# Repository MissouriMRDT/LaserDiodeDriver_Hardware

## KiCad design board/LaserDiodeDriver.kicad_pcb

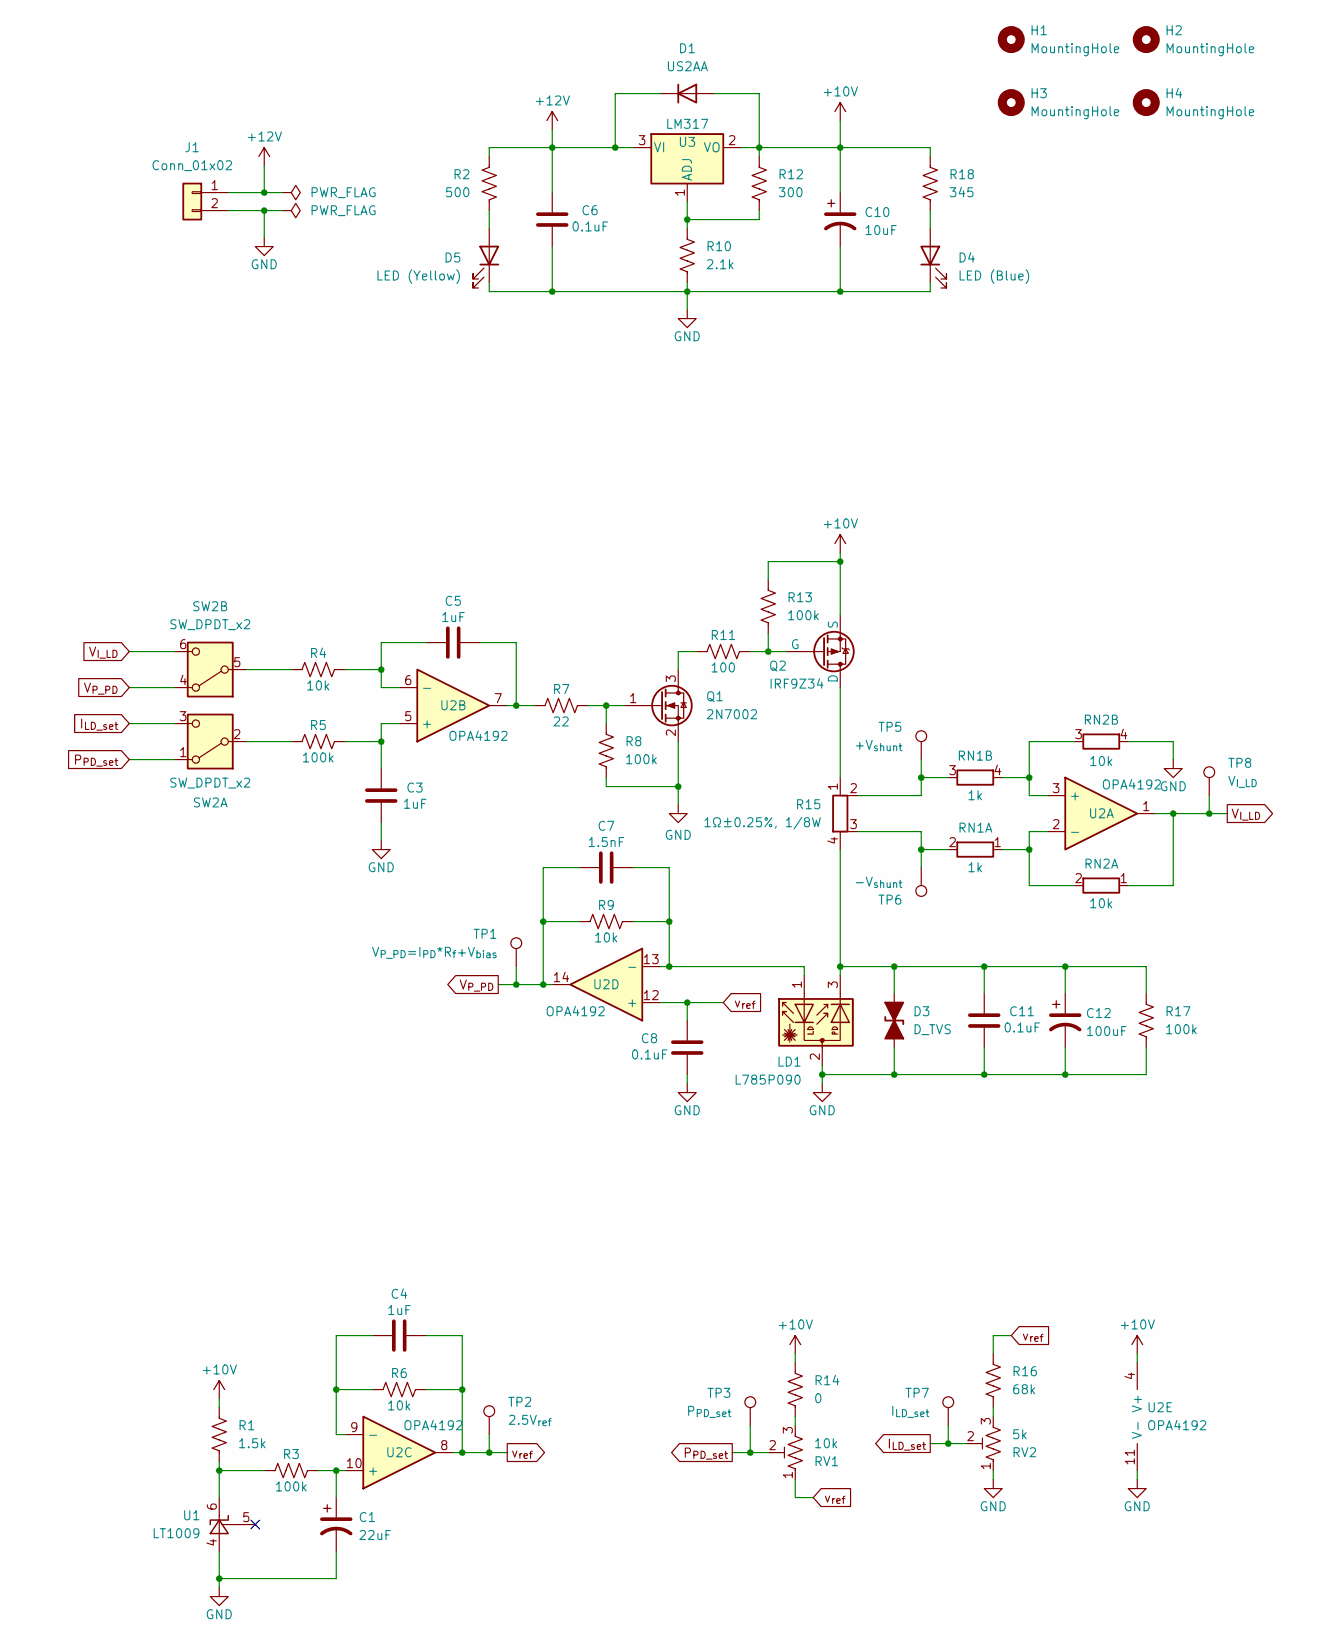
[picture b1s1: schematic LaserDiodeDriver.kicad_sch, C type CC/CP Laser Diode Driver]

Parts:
C1: 22uF; CP_Elec_5x5.8
C3, C4, C5: 1uF; C_0603_1608Metric
C6, C8, C11: 0.1uF; C_0603_1608Metric
C7: 1.5nF; C_0603_1608Metric
C10: 10uF; CP_Elec_5x5.8
C12: 100uF; CP_Elec_6.3x5.8
D1: US2AA; D_SMA
D3: D_TVS; D_0603_1608Metric
D4: LED (Blue); LED_0603_1608Metric
D5: LED (Yellow); LED_0603_1608Metric
H1, H2, H3, H4: MountingHole; Mounting_Wuerth_WA-SMSI-M1.6_H4.5mm_ThreadDepth2mm_97730456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
J1: Conn_01x02; JST_EH_S2B-EH_1x02_P2.50mm_Horizontal
LD1: L785P090; S7060R - Laser Diode Socket for Ø5.6 mm Laser, 3 Pin
Q1: 2N7002; SOT-23
Q2: IRF9Z34; TO-220-3_Horizontal_TabUp
R1: 1.5k; R_0603_1608Metric
R2: 500; R_0603_1608Metric
R3, R5, R8, R13, R17: 100k; R_0603_1608Metric
R4, R6, R9: 10k; R_0603_1608Metric
R7: 22; R_0603_1608Metric
R10: 2.1k; R_0603_1608Metric
R11: 100; R_0603_1608Metric
R12: 300; R_0603_1608Metric
R14: 0; R_0603_1608Metric_Pad0.98x0.95mm_HandSolder
R15: 1Ω±0.25%, 1/8W; R_Shunt_0805_2012Metric
R16: 68k; R_0603_1608Metric_Pad0.98x0.95mm_HandSolder
R18: 345; R_0603_1608Metric
RN1: 1k; R_Array_Convex_2x0606
RN2: 10k; R_Array_Convex_2x0606
RV1: 10k; Potentiometer_Bourns_3296W_Vertical
RV2: 5k; Potentiometer_Bourns_3296Y_Vertical
SW2: SW_DPDT_x2; SW_DPDT_CK_JS202011JCQN
TP1: V_{P_PD}=I_{PD}*R_{f}+V_{bias}; TestPoint_Pad_D1.5mm
TP2: 2.5V_{ref}; TestPoint_Pad_D1.5mm
TP3: P_{PD_set}; TestPoint_Pad_D1.5mm
TP5: +V_{shunt}; TestPoint_Pad_D1.5mm
TP6: -V_{shunt}; TestPoint_Pad_D1.5mm
TP7: I_{LD_set}; TestPoint_Pad_D1.5mm
TP8: V_{I_LD}; TestPoint_Pad_D1.5mm
U1: LT1009; SOIC-8_3.9x4.9mm_P1.27mm
U2: OPA4192; SOIC-14_3.9x8.7mm_P1.27mm
U3: LM317; TO-220-3_Horizontal_TabUp

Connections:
+10V: C10.1, D1.2 (A), Q2.3 (S), R1.1, R12.1, R13.1, R14.1, R18.1, U2.4 (V+), U3.2 (VO)
+12V: C6.1, D1.1 (K), J1.1, R2.1, U3.3 (VI)
GND: C1.2, C3.1, C6.2, C8.2, C10.2, C11.2, C12.2, D3.1 (A1), D4.1 (K), D5.1 (K), J1.2, LD1.2, Q1.2 (S), R8.2, R10.2, R17.2, RN2.4 (R2.2), RV2.1, U1.4 (A), U2.11 (V-)
I_{LD_set}: RV2.2, SW2.3 (C), TP7.1
unnamed: C5.2, R7.1, U2.7
unnamed: C11.1, C12.1, D3.2 (A2), LD1.3, R15.4, R17.1
unnamed: D4.2 (A), R18.2
unnamed: D5.2 (A), R2.2
unnamed: Q1.3 (D), R11.1
unnamed: Q1.1 (G), R7.2, R8.1
unnamed: Q2.1 (D), R15.1
unnamed: Q2.2 (G), R11.2, R13.2
unnamed: R1.2, R3.1, U1.6 (K), U1.8 (K)
unnamed: R14.2, RV1.3
unnamed: R16.2, RV2.3
unnamed: RN1.1 (R1.1), RN2.2 (R1.2), U2.2 (-)
unnamed: R15.3, RN1.2 (R1.2), TP6.1
unnamed: R15.2, RN1.3 (R2.1), TP5.1
unnamed: RN1.4 (R2.2), RN2.3 (R2.1), U2.3 (+)
unnamed: R5.1, SW2.2 (B)
unnamed: R4.1, SW2.5 (B)
unnamed: C3.2, R5.2, U2.5 (+)
unnamed: C5.1, R4.2, U2.6 (-)
unnamed: C1.1, R3.2, U2.10 (+)
unnamed: C4.1, R6.1, U2.9 (-)
unnamed: C7.2, LD1.1, R9.2, U2.13 (-)
unnamed: R10.1, R12.2, U3.1 (ADJ)
P_{PD_set}: RV1.2, SW2.1 (A), TP3.1
V_{I_LD}: RN2.1 (R1.1), SW2.6 (C), TP8.1, U2.1
V_{P_PD}: C7.1, R9.1, SW2.4 (A), TP1.1, U2.14
v_{ref}: C4.2, C8.1, R6.2, R16.1, RV1.1, TP2.1, U2.8, U2.12 (+)

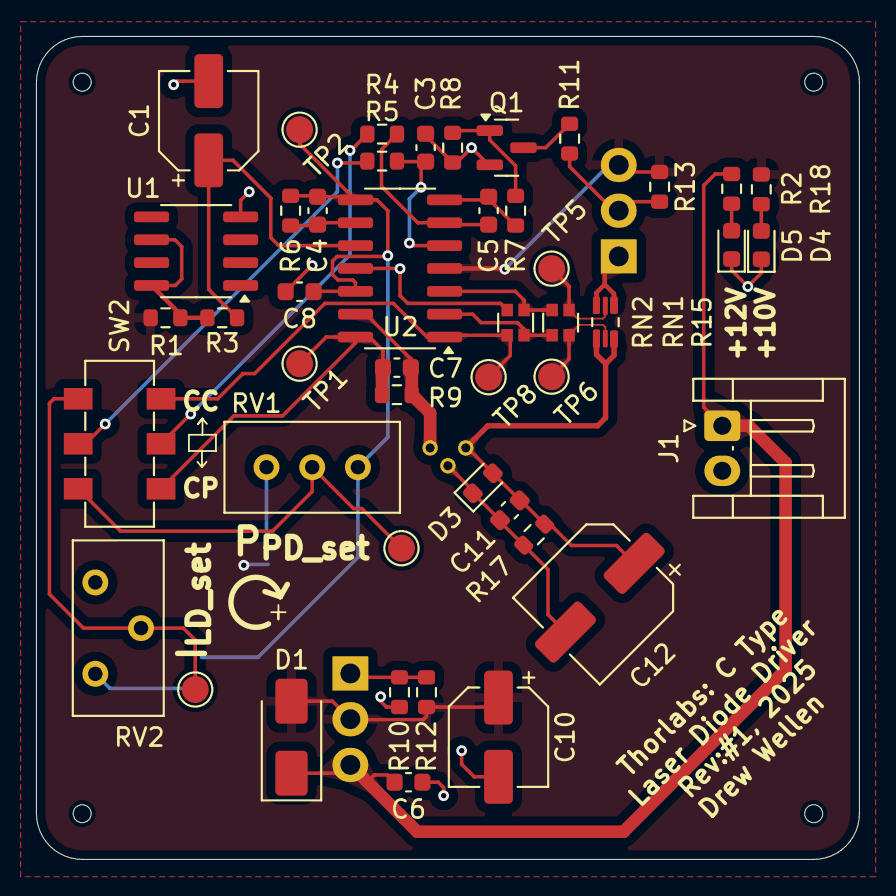
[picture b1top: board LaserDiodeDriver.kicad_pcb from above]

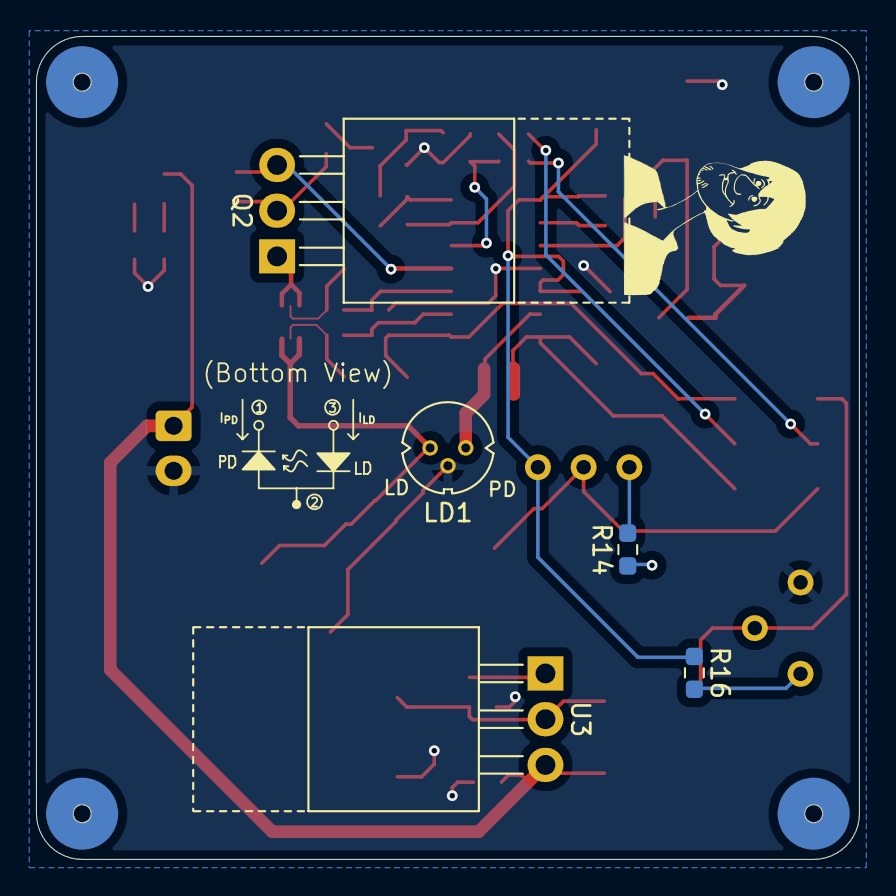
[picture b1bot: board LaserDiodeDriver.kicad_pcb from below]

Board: 2 copper layers, 45.7 x 45.7 mm, 55 parts (9 on the bottom side), 31 nets.

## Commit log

2025-09-07 Added existing schematic
2025-09-15 Updated Parts and Proc'd them
2025-09-16 General changes
2025-09-30 Test circuit
    Started designing the initial test circuit with LM358s to verify the working of a basic P-channel current drive circuit.
2025-10-01 More tweaks to high side current control test circuit
2025-10-02 Designed/Tested a working cathode ground high side current source
2025-10-02 Organizing/editing different circuits
2025-10-03 Move all the test schematics to a local file and started design of the one that will be a board.
2025-10-10 Imported proper working circuit in preparation for layout
2025-10-11 Made/tested LM317 circuit
    The LM317 was configured for 12V input and 6V output to power the main laser driver circuit. With a high power LED as a stand in for the laser diode and current set to 125mA, the power dissipation of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
2025-10-12 Various changes (read description for info)
    * Changed LM317 output voltage to be 10V since testing at that voltage reduced heat dissipation across shunt, LM317, and current drive FET.
    * Deleted test schematic
    * Swapped 1Ohm shunt to five 5Ohm SMD resistors with +_50ppm/*C at 1% tolerance to distribute heat load and average out tolerances.
    * Found proper quad symbol for OP-amp and inserted datasheet + footprint.
2025-10-12 Calculating proper values/picking components
    * Calculated values needed for differential amplifier and Vref max setpoint resistor.
    * Added datasheets, footprints, and descriptions for various parts like pots, shunts, and FET.
    * Tested differential amplifier values on breadboard.
2025-10-14 Constant power loop
    This new circuit uses the same format of constant current loop but now there is a second control loop that can be switched on with a reed relay to incorporate power feedback of the photodiode. This i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
2025-10-14 Idea for differential integrator in one op-amp
2025-10-15 Lots of testing schematics. I am brain dead. Guhhhh
2025-10-15 Tested non-inverting amplifier with offset and confirmed diff amp feedback implausible.
2025-10-16 Tested diff-amp input for gate drive op-amp and added in a summing amplifier to test
2025-10-16 Trying new negative differential feedback for constant power control
2025-10-17 Designed a solid method of photodiode feedback
    This method utilizes a diff-amp with an offset voltage where the photocurrent feedback subtracts from a setpoint and added to the offset to create the current setpoint and regulate the photodiode pow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
2025-10-18 AMAZING DEVELOPMENT!!!
    All of this troubleshooting and different design things come down to a sign issue. It's the fact that the P-channel MOSFET turns off more with a higher voltage at the gate. SO the gate drive op-amp h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
2025-10-18 Got rid of extra schematics and changed page settings
2025-10-18 Tested diff-amp feedback with pull-down transistor for gate driving current control FET. Works!
2025-10-19 Moved diff-amp low to P-channel MOSFET and reduced gain setting resistor values to improve CMRR.
2025-10-20 Eliminated need for mid-rail buffer and cleaned up page. Corrected setpoints.
2025-10-20 Various housekeeping changes
    * Re-did entire schematic to ensure all connections good
    * Added description, datasheet, price, footprint, and part # for almost all parts
    * Cleaned up schematic in general
2025-10-20 Swapped to different signal relay
    Since the signal relay is so large relative to all other components, It may be better to find an alternative. Something quicker than 0 Ohm jumpers but smaller than a telecoms signal relay that still 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
2025-10-20 Added heatsink for P-FET and LM317, slide switch, and power connector
2025-10-20 Found rectifier diode and ensured things fit to begin layout
2025-10-20 Got a footprint, description, price, and datasheet for all parts except laser diode socket
2025-10-21 Made custom footprint/3D model for laser diode socket
2025-10-21 Set height of objects and began rough layout
2025-10-21 Shunt Sense footprint
2025-10-21 Trying goofy layout things
2025-10-21 Final pricing of components $44.88
2025-10-22 Added shunt 3D model
2025-10-22 Changed gate drive feedback capacitor and tested constant power control. Needs improvement.
2025-10-22 Imported power connector models and info.
2025-10-23 Layout of differential amplifier, TIA, and laser diode.
2025-10-23 Added laser diode 3D file and more layout
2025-10-25 Various changes + component placement
    * Removed signal relay in favor of SPDT switch in the interest of space.
    * Placed components for optimal mechanical mounting with LD in center of PCB.
    * Got rid of LM317 pot for space calculated proper values for LM317 to be +10V output.
    * Arranged resistors for good placement.
2025-10-29 Updated switch footprint and added GND filled zone on back.
2025-10-30 Finished Layout
2025-10-30 Added pot indicator silkscreen
2025-10-30 Final touches :)
2025-10-30 Final Final touches. Added indicator LEDs.
2025-10-30 Added date to silkscreen
2025-10-31 Layout review initial changes
2025-11-02 Post layout review fixes. Ready for CDR and ordering
2025-11-11 Add github workflow
2025-11-30 Eliminated unavailable capacitor for a second 10uF electrolytic
2025-12-03 Generated .STEP file
2025-12-07 Flipped laser diode symbol back
2025-12-08 Started simulations in LTspice
2025-12-09 Simulation adjustments and setpoint resistor fixed
2025-12-12 Measured photocurrent and change R14 accordingly
2026-03-15 Began design of rev2
2026-03-15 Added buck components
2026-03-15 Buck converter component selection
2026-03-16 Finished buck converter
2026-03-16 Smaller inductor chosen
2026-03-16 Removed duplicate models
2026-03-16 Moved Rev1 models to Rev2 3D file
2026-03-16 Changed LD for JST connector
